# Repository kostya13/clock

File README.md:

Электронные часы на базе ATTiny2313 и часов DS1307.

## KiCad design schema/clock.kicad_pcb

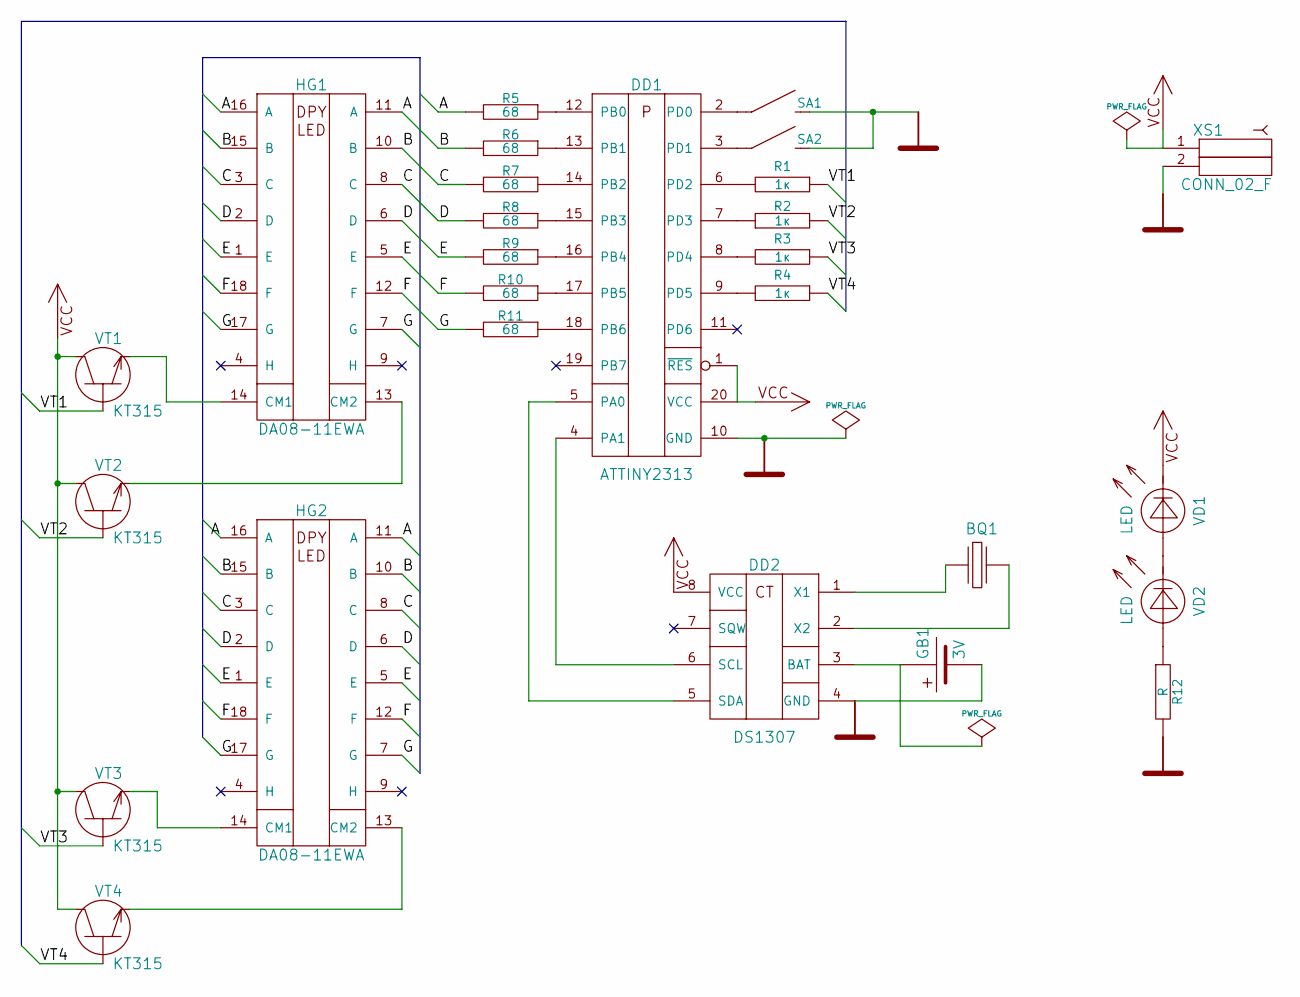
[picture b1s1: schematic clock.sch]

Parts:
BQ1: CRYSTAL
DD1: ATTINY2313
DD2: DS1307
GB1: 3V
HG1, HG2: DA08-11EWA
R1, R2, R3, R4: 1к
R5, R6, R7, R8, R9, R10, R11: 68
R12: R
SA1, SA2: SA_1-2_CL
VD1, VD2: LED
VT1, VT2, VT3, VT4: КТ315
XS1: CONN_02_F

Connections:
/A: HG1.11 (A), HG1.16 (A), HG2.11 (A), HG2.16 (A), R5.2
/B: HG1.10 (B), HG1.15 (B), HG2.10 (B), HG2.15 (B), R6.2
/C: HG1.3 (C), HG1.8 (C), HG2.3 (C), HG2.8 (C), R7.2
/D: HG1.2 (D), HG1.6 (D), HG2.2 (D), HG2.6 (D), R8.2
/E: HG1.1 (E), HG1.5 (E), HG2.1 (E), HG2.5 (E), R9.2
/F: HG1.12 (F), HG1.18 (F), HG2.12 (F), HG2.18 (F), R10.2
/G: HG1.7 (G), HG1.17 (G), HG2.7 (G), HG2.17 (G), R11.2
/VT1: R1.1, VT1.1 (B)
/VT2: R2.2, VT2.1 (B)
/VT3: R3.1, VT3.1 (B)
/VT4: R4.1, VT4.1 (B)
GND: DD1.10 (GND), DD2.4 (GND), GB1.2 (-), R12.2, SA1.1, SA2.1, XS1.2
unnamed: DD1.5 (PA0), DD2.5 (SDA)
unnamed: DD1.4 (PA1), DD2.6 (SCL)
unnamed: BQ1.2, DD2.2 (X2)
unnamed: BQ1.1, DD2.1 (X1)
unnamed: HG2.14 (CM1), VT3.3 (E)
unnamed: HG2.13 (CM2), VT4.3 (E)
unnamed: HG1.13 (CM2), VT2.3 (E)
unnamed: HG1.14 (CM1), VT1.3 (E)
unnamed: DD2.3 (BAT), GB1.1 (+)
unnamed: VD1.2, VD2.1
unnamed: R12.1, VD2.2
unnamed: DD1.16 (PB4), R9.1
unnamed: DD1.17 (PB5), R10.1
unnamed: DD1.18 (PB6), R11.1
unnamed: DD1.15 (PB3), R8.1
unnamed: DD1.3 (PD1), SA2.2
unnamed: DD1.2 (PD0), SA1.2
unnamed: DD1.7 (PD3), R2.1
unnamed: DD1.6 (PD2), R1.2
unnamed: DD1.8 (PD4), R3.2
unnamed: DD1.9 (PD5), R4.2
unnamed: DD1.12 (PB0), R5.1
unnamed: DD1.13 (PB1), R6.1
unnamed: DD1.14 (PB2), R7.1
VCC: DD1.1 (~RES), DD1.20 (VCC), DD2.8 (VCC), VD1.1, VT1.2 (C), VT2.2 (C), VT3.2 (C), VT4.2 (C), XS1.1

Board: 2 copper layers, 27 parts (0 on the bottom side), 37 nets, no tracks yet.

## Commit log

2014-03-12 next step
2014-03-20 edit
2014-03-24 check errors
2017-02-23 README.md edited online with Bitbucket
